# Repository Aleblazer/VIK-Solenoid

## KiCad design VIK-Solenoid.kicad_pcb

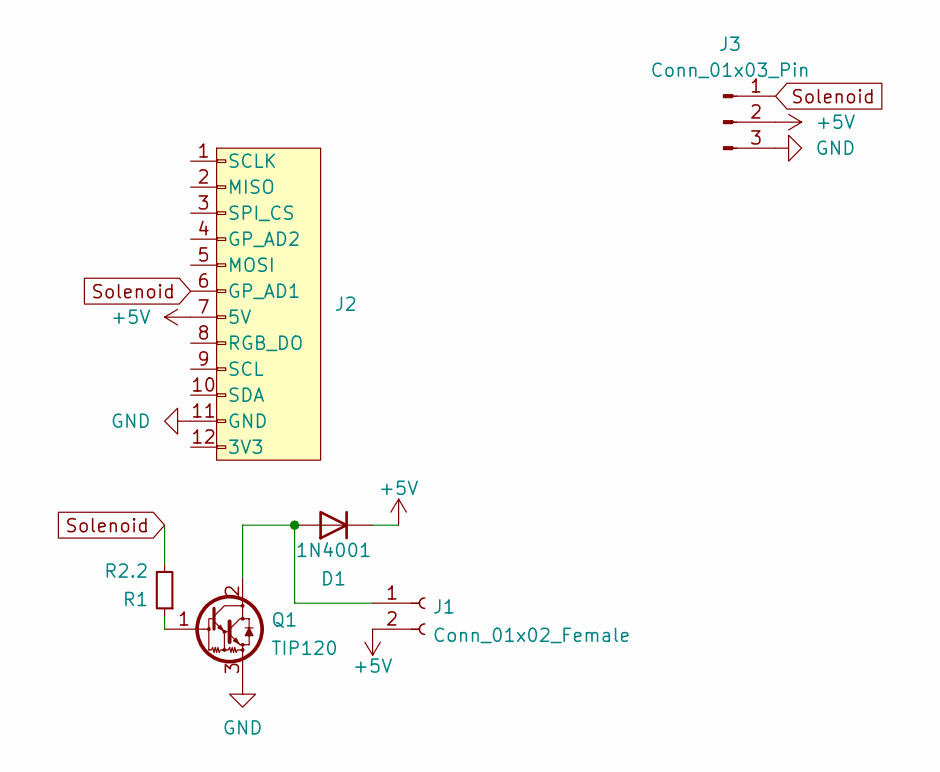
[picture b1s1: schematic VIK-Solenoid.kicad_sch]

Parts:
D1: 1N4001; D_SOD-123F
J1: Conn_01x02_Female; PinHeader_1x02_P2.54mm_Vertical
J2: vik-module-connector; vik-module-connector-horizontal-mini
J3: Conn_01x03_Pin; PinHeader_1x03_P2.54mm_Vertical
Q1: TIP120; TO-252-2
R1: R2.2; R_1206_3216Metric

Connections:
+5V: D1.1 (K), J1.2, J2.7 (5V), J3.2
GND: J2.11 (GND), J3.3, Q1.3 (E)
unnamed: D1.2 (A), J1.1, Q1.2 (C)
unnamed: Q1.1 (B), R1.1
Solenoid: J2.6 (GP_AD1), J3.1, R1.2

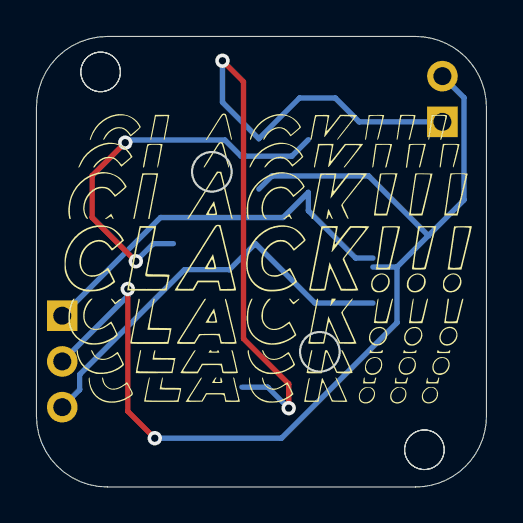
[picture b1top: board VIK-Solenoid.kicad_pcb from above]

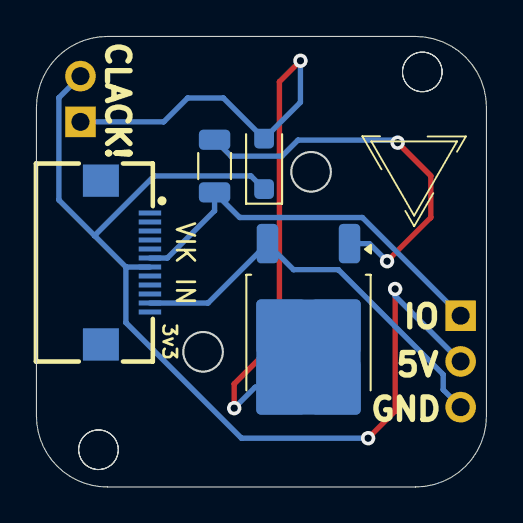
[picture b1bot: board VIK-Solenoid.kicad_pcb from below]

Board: 2 copper layers, 25.0 x 25.0 mm, 6 parts (4 on the bottom side), 5 nets.

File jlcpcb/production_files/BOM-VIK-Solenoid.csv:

Comment,Designator,Footprint,LCSC
1N4001,D1,D_SOD-123F,C2892326
vik-module-connector,J2,vik-module-connector-horizontal-mini,C2919479
R2.2,R1,R_1206_3216Metric,C325909
TIP120,Q1,TO-252-2,C59488

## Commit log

2024-06-16 Final Version with productions files
    Added JLCPCB production files.
2024-06-16 XS version
    Extra Small Variant
